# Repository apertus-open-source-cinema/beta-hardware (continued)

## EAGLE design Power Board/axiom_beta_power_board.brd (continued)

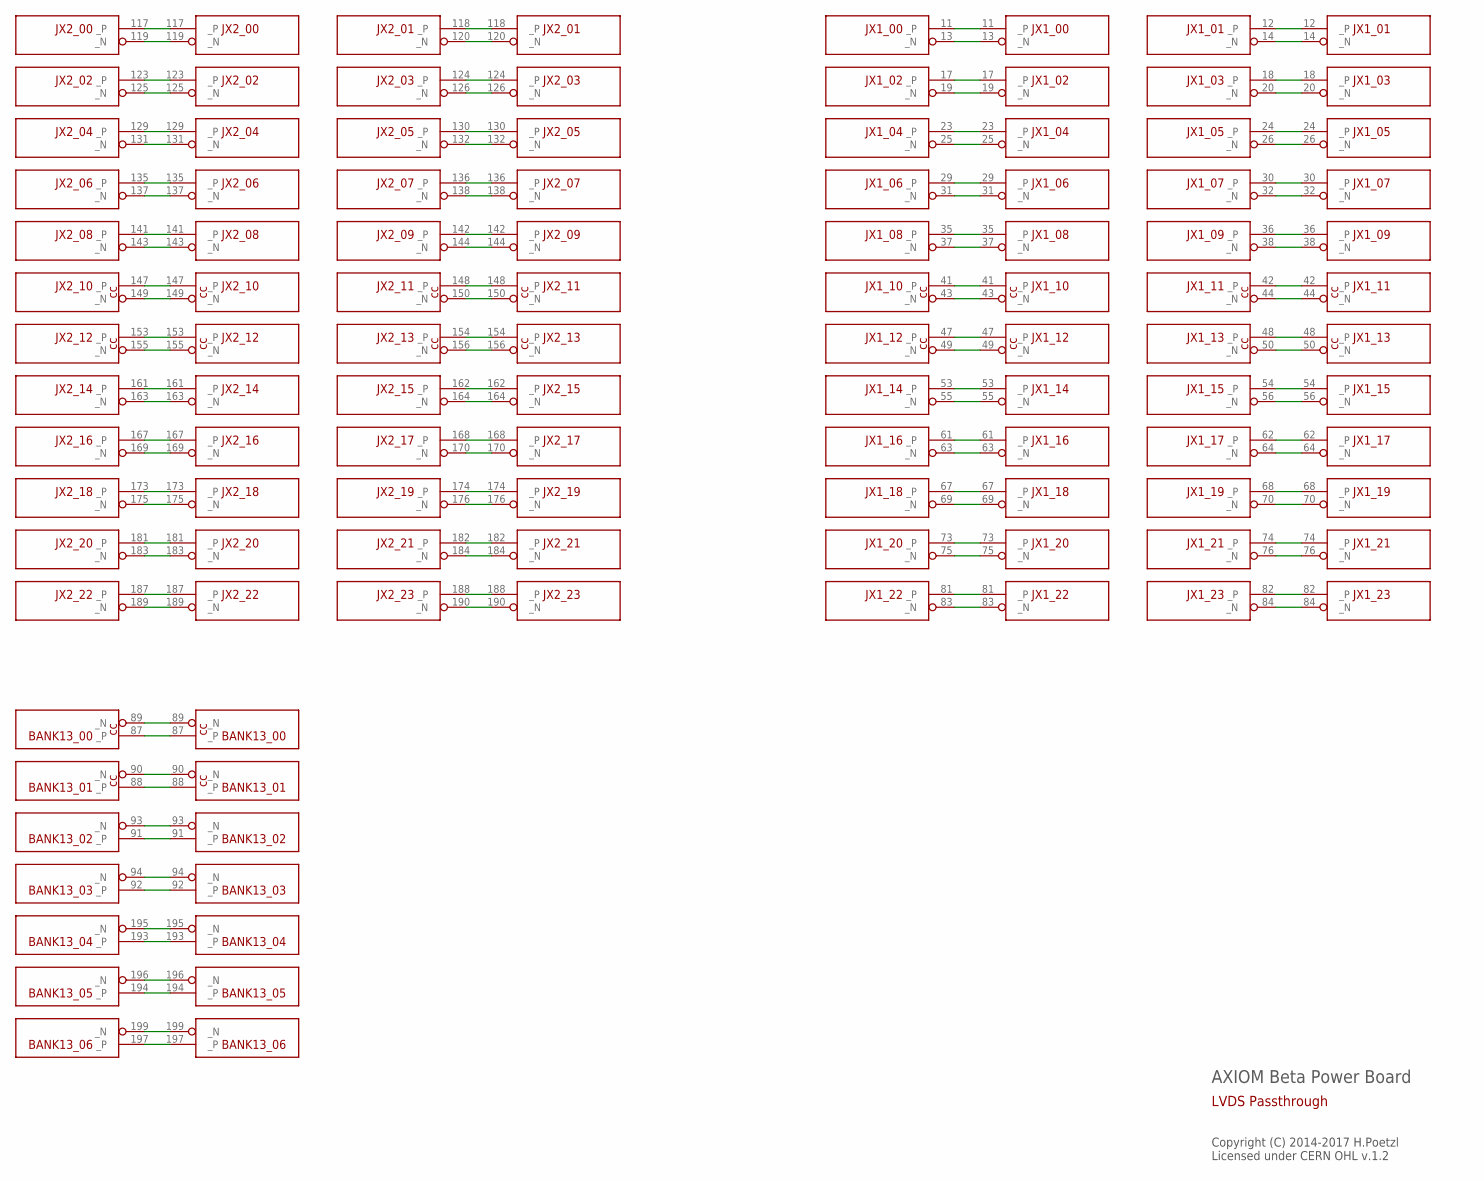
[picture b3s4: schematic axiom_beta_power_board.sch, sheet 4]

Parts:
BETA: µZ-FCI-SOCKET-NOHOLES-R; µZ-SOCKET-NOHOLES-R
ZED: µZ-FCI-CONONLY; µZ-CONONLY

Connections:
BANK13_00_N: BETA.89 (_N), ZED.89 (_N)
BANK13_00_P: BETA.87 (_P), ZED.87 (_P)
BANK13_01_N: BETA.90 (_N), ZED.90 (_N)
BANK13_01_P: BETA.88 (_P), ZED.88 (_P)
BANK13_02_N: BETA.93 (_N), ZED.93 (_N)
BANK13_02_P: BETA.91 (_P), ZED.91 (_P)
BANK13_03_N: BETA.94 (_N), ZED.94 (_N)
BANK13_03_P: BETA.92 (_P), ZED.92 (_P)
BANK13_04_N: BETA.195 (_N), ZED.195 (_N)
BANK13_04_P: BETA.193 (_P), ZED.193 (_P)
BANK13_05_N: BETA.196 (_N), ZED.196 (_N)
BANK13_05_P: BETA.194 (_P), ZED.194 (_P)
BANK13_06_N: BETA.199 (_N), ZED.199 (_N)
BANK13_06_P: BETA.197 (_P), ZED.197 (_P)
JX1_00_N: BETA.13 (_N), ZED.13 (_N)
JX1_00_P: BETA.11 (_P), ZED.11 (_P)
JX1_01_N: BETA.14 (_N), ZED.14 (_N)
JX1_01_P: BETA.12 (_P), ZED.12 (_P)
JX1_02_N: BETA.19 (_N), ZED.19 (_N)
JX1_02_P: BETA.17 (_P), ZED.17 (_P)
JX1_03_N: BETA.20 (_N), ZED.20 (_N)
JX1_03_P: BETA.18 (_P), ZED.18 (_P)
JX1_04_N: BETA.25 (_N), ZED.25 (_N)
JX1_04_P: BETA.23 (_P), ZED.23 (_P)
JX1_05_N: BETA.26 (_N), ZED.26 (_N)
JX1_05_P: BETA.24 (_P), ZED.24 (_P)
JX1_06_N: BETA.31 (_N), ZED.31 (_N)
JX1_06_P: BETA.29 (_P), ZED.29 (_P)
JX1_07_N: BETA.32 (_N), ZED.32 (_N)
JX1_07_P: BETA.30 (_P), ZED.30 (_P)
JX1_08_N: BETA.37 (_N), ZED.37 (_N)
JX1_08_P: BETA.35 (_P), ZED.35 (_P)
JX1_09_N: BETA.38 (_N), ZED.38 (_N)
JX1_09_P: BETA.36 (_P), ZED.36 (_P)
JX1_10_N: BETA.43 (_N), ZED.43 (_N)
JX1_10_P: BETA.41 (_P), ZED.41 (_P)
JX1_11_N: BETA.44 (_N), ZED.44 (_N)
JX1_11_P: BETA.42 (_P), ZED.42 (_P)
JX1_12_N: BETA.49 (_N), ZED.49 (_N)
JX1_12_P: BETA.47 (_P), ZED.47 (_P)
JX1_13_N: BETA.50 (_N), ZED.50 (_N)
JX1_13_P: BETA.48 (_P), ZED.48 (_P)
JX1_14_N: BETA.55 (_N), ZED.55 (_N)
JX1_14_P: BETA.53 (_P), ZED.53 (_P)
JX1_15_N: BETA.56 (_N), ZED.56 (_N)
JX1_15_P: BETA.54 (_P), ZED.54 (_P)
JX1_16_N: BETA.63 (_N), ZED.63 (_N)
JX1_16_P: BETA.61 (_P), ZED.61 (_P)
JX1_17_N: BETA.64 (_N), ZED.64 (_N)
JX1_17_P: BETA.62 (_P), ZED.62 (_P)
JX1_18_N: BETA.69 (_N), ZED.69 (_N)
JX1_18_P: BETA.67 (_P), ZED.67 (_P)
JX1_19_N: BETA.70 (_N), ZED.70 (_N)
JX1_19_P: BETA.68 (_P), ZED.68 (_P)
JX1_20_N: BETA.75 (_N), ZED.75 (_N)
JX1_20_P: BETA.73 (_P), ZED.73 (_P)
JX1_21_N: BETA.76 (_N), ZED.76 (_N)
JX1_21_P: BETA.74 (_P), ZED.74 (_P)
JX1_22_N: BETA.83 (_N), ZED.83 (_N)
JX1_22_P: BETA.81 (_P), ZED.81 (_P)
JX1_23_N: BETA.84 (_N), ZED.84 (_N)
JX1_23_P: BETA.82 (_P), ZED.82 (_P)
JX2_00_N: BETA.119 (_N), ZED.119 (_N)
JX2_00_P: BETA.117 (_P), ZED.117 (_P)
JX2_01_N: BETA.120 (_N), ZED.120 (_N)
JX2_01_P: BETA.118 (_P), ZED.118 (_P)
JX2_02_N: BETA.125 (_N), ZED.125 (_N)
JX2_02_P: BETA.123 (_P), ZED.123 (_P)
JX2_03_N: BETA.126 (_N), ZED.126 (_N)
JX2_03_P: BETA.124 (_P), ZED.124 (_P)
JX2_04_N: BETA.131 (_N), ZED.131 (_N)
JX2_04_P: BETA.129 (_P), ZED.129 (_P)
JX2_05_N: BETA.132 (_N), ZED.132 (_N)
JX2_05_P: BETA.130 (_P), ZED.130 (_P)
JX2_06_N: BETA.137 (_N), ZED.137 (_N)
JX2_06_P: BETA.135 (_P), ZED.135 (_P)
JX2_07_N: BETA.138 (_N), ZED.138 (_N)
JX2_07_P: BETA.136 (_P), ZED.136 (_P)
JX2_08_N: BETA.143 (_N), ZED.143 (_N)
JX2_08_P: BETA.141 (_P), ZED.141 (_P)
JX2_09_N: BETA.144 (_N), ZED.144 (_N)
JX2_09_P: BETA.142 (_P), ZED.142 (_P)
JX2_10_N: BETA.149 (_N), ZED.149 (_N)
JX2_10_P: BETA.147 (_P), ZED.147 (_P)
JX2_11_N: BETA.150 (_N), ZED.150 (_N)
JX2_11_P: BETA.148 (_P), ZED.148 (_P)
JX2_12_N: BETA.155 (_N), ZED.155 (_N)
JX2_12_P: BETA.153 (_P), ZED.153 (_P)
JX2_13_N: BETA.156 (_N), ZED.156 (_N)
JX2_13_P: BETA.154 (_P), ZED.154 (_P)
JX2_14_N: BETA.163 (_N), ZED.163 (_N)
JX2_14_P: BETA.161 (_P), ZED.161 (_P)
JX2_15_N: BETA.164 (_N), ZED.164 (_N)
JX2_15_P: BETA.162 (_P), ZED.162 (_P)
JX2_16_N: BETA.169 (_N), ZED.169 (_N)
JX2_16_P: BETA.167 (_P), ZED.167 (_P)
JX2_17_N: BETA.170 (_N), ZED.170 (_N)
JX2_17_P: BETA.168 (_P), ZED.168 (_P)
JX2_18_N: BETA.175 (_N), ZED.175 (_N)
JX2_18_P: BETA.173 (_P), ZED.173 (_P)
JX2_19_N: BETA.176 (_N), ZED.176 (_N)
JX2_19_P: BETA.174 (_P), ZED.174 (_P)
JX2_20_N: BETA.183 (_N), ZED.183 (_N)
JX2_20_P: BETA.181 (_P), ZED.181 (_P)
JX2_21_N: BETA.184 (_N), ZED.184 (_N)
JX2_21_P: BETA.182 (_P), ZED.182 (_P)
JX2_22_N: BETA.189 (_N), ZED.189 (_N)
JX2_22_P: BETA.187 (_P), ZED.187 (_P)
JX2_23_N: BETA.190 (_N), ZED.190 (_N)
JX2_23_P: BETA.188 (_P), ZED.188 (_P)

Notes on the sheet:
AXIOM Beta Power Board
Copyright (C) 2014-2017 H.Poetzl Licensed under CERN OHL v.1.2
LVDS Passthrough

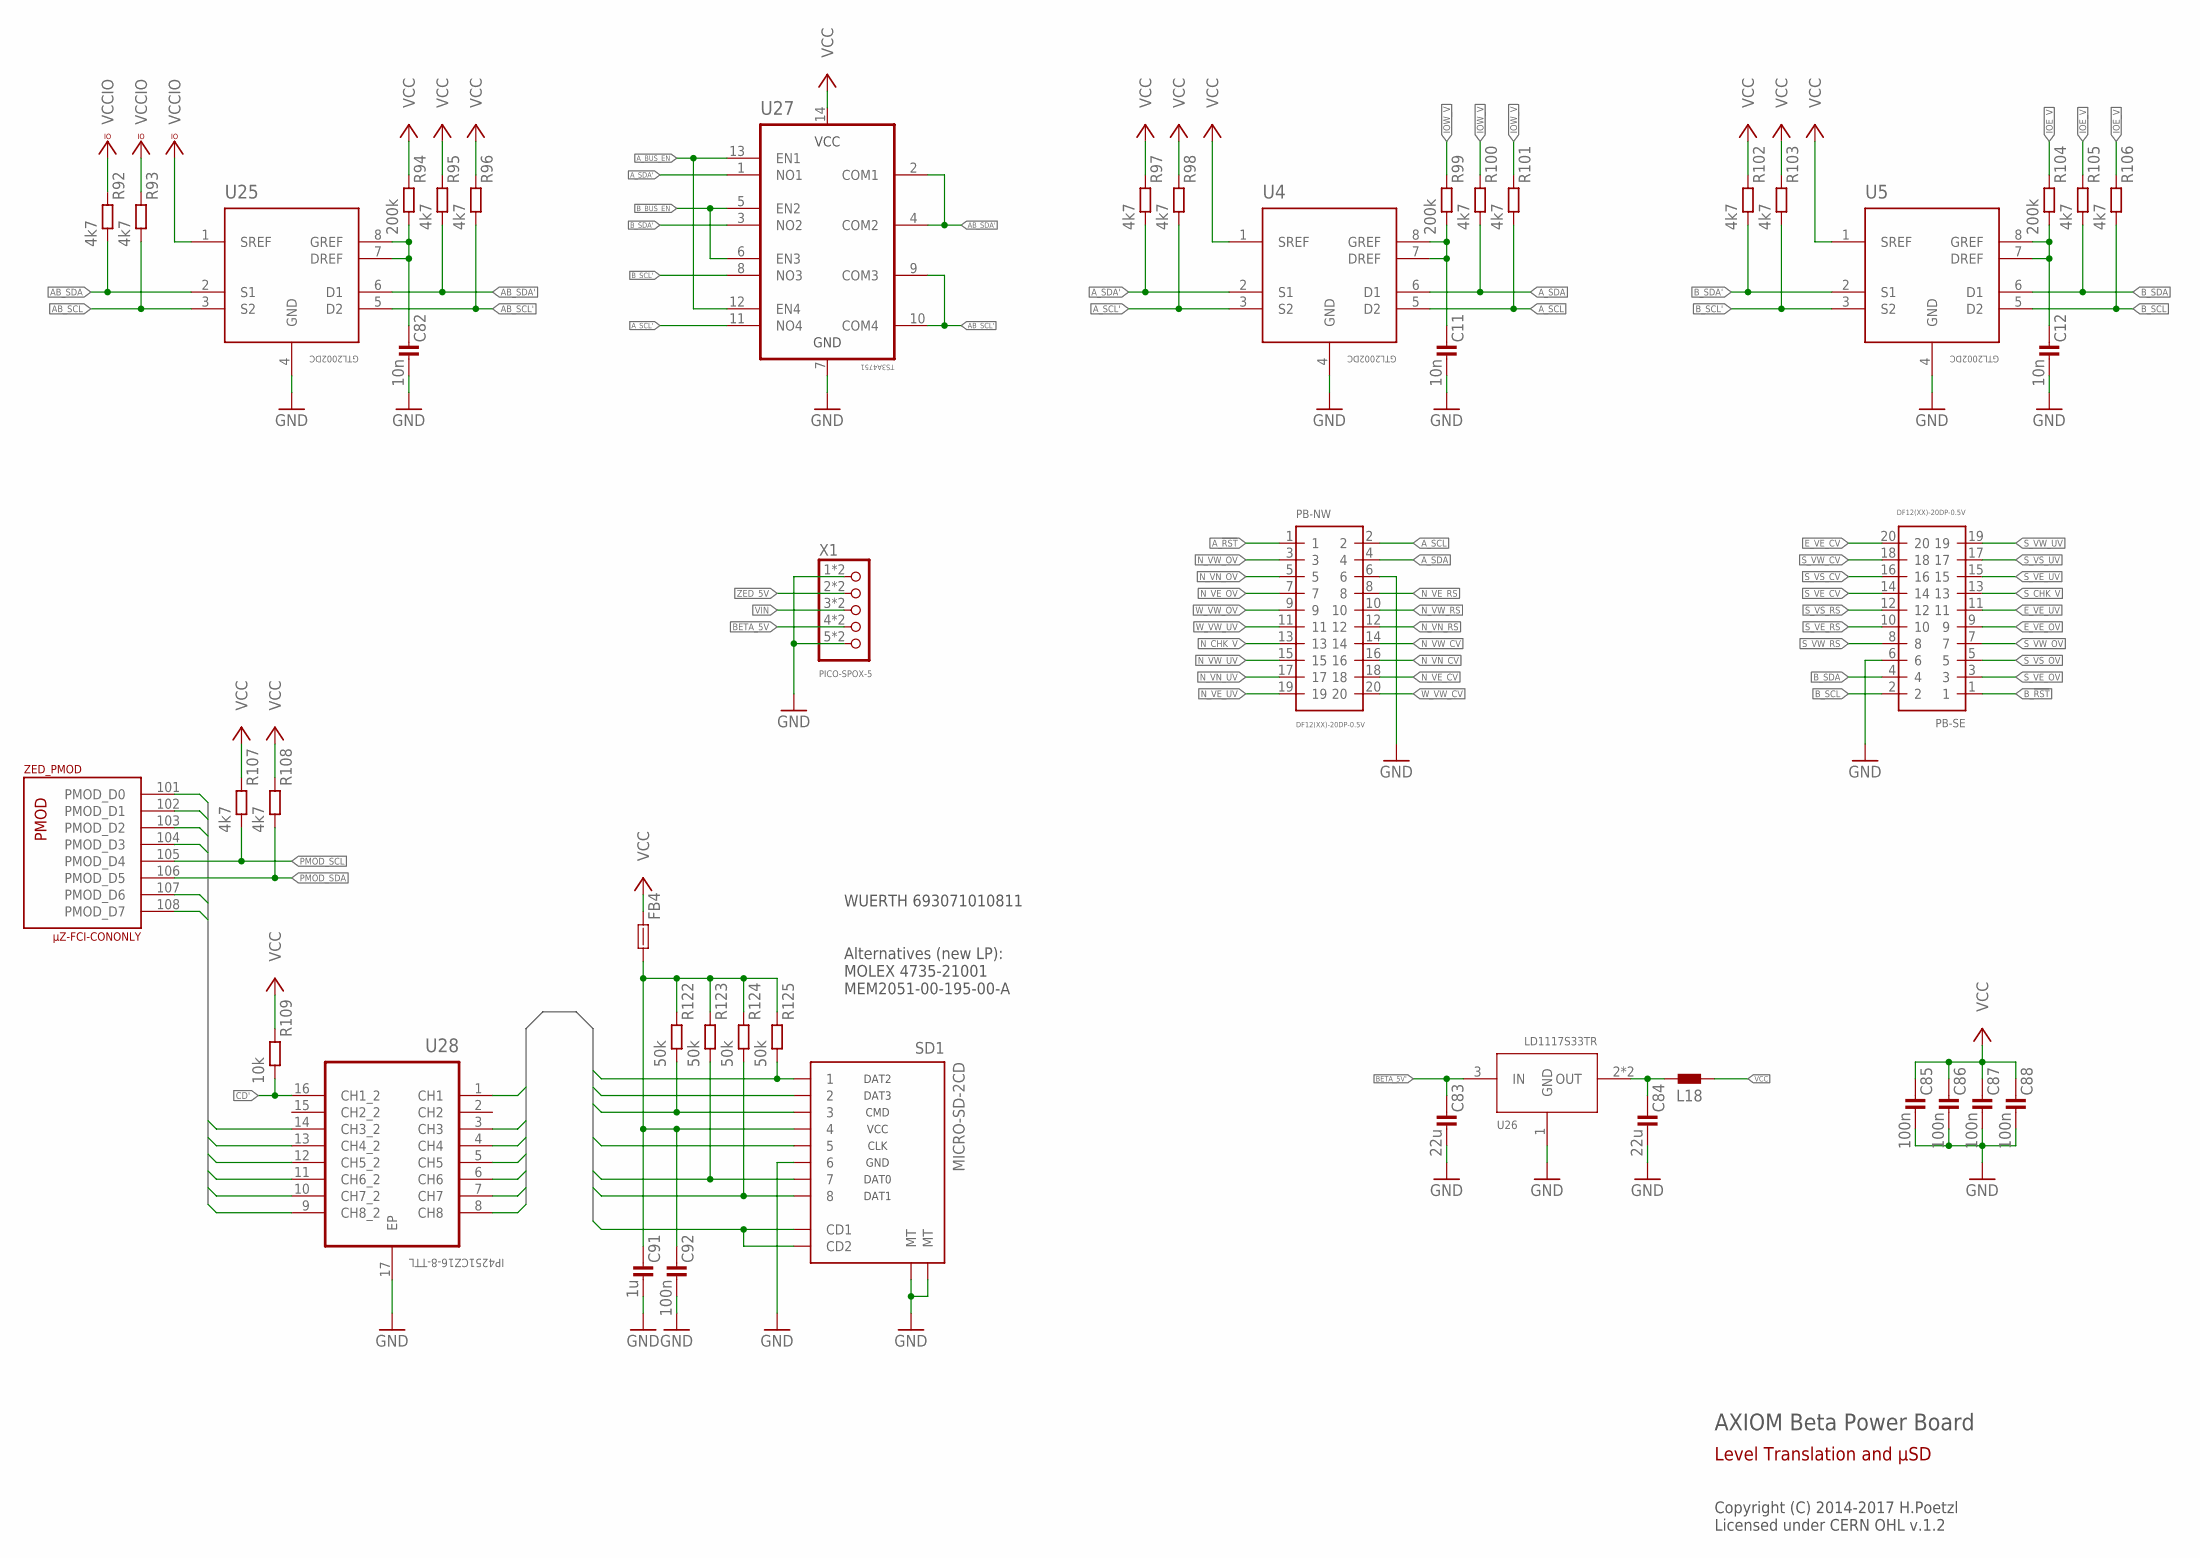
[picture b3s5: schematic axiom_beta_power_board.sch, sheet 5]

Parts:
C11, C12, C82: 10n; 0402-B
C83, C84: 22u; 0805-B
C85, C86, C87, C88, C92: 100n; 0402-B
C91: 1u; 0402-B
FB4: FB0402-B; 0402-B
L18: L0805-A; 0805-A
PB-NW: DF12(XX)-20DP-0.5V
PB-SE: DF12(XX)-20DP-0.5V
R92, R93, R95, R96, R97, R98, R100, R101, R102, R103, R105, R106, R107, R108: 4k7; 0402-B
R94, R99, R104: 200k; 0402-B
R109: 10k; 0402-B
R122, R123, R124, R125: 50k; 0402-B
SD1: MICRO-SD-2CD; TF-MICRO-SD_PP2
U4, U5, U25: GTL2002DC; VSSOP-8
U26: LD1117S33TR; SOT-223
U27: TS3A4751; SOP65P640X120-14N
U28: IP4251CZ16-8-TTL; SON40P135X330X55-17N
X1: PICO-SPOX-5
ZED: µZ-FCI-CONONLY; µZ-CONONLY

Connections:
AB_SCL: R93.2, U25.3 (S2); also elsewhere on the board
AB_SCL': R96.2, U25.5 (D2), U27.9 (COM3), U27.10 (COM4)
AB_SDA: R92.2, U25.2 (S1); also elsewhere on the board
AB_SDA': R95.2, U25.6 (D1), U27.2 (COM1), U27.4 (COM2)
A_!RST: PB-NW.1; also elsewhere on the board
A_BUS_EN: U27.12 (EN4), U27.13 (EN1); also elsewhere on the board
A_SCL: PB-NW.2, R101.2, U4.5 (D2)
A_SCL': R98.2, U4.3 (S2), U27.11 (NO4)
A_SDA: PB-NW.4, R100.2, U4.6 (D1)
A_SDA': R97.2, U4.2 (S1), U27.1 (NO1)
BETA_5V: X1.4, X1.4A (4); also elsewhere on the board
BETA_5V': C83.1, U26.3 (IN); also elsewhere on the board
B_!RST: PB-SE.1; also elsewhere on the board
B_BUS_EN: U27.5 (EN2), U27.6 (EN3); also elsewhere on the board
B_SCL: PB-SE.2, R106.2, U5.5 (D2)
B_SCL': R103.2, U5.3 (S2), U27.8 (NO3)
B_SDA: PB-SE.4, R105.2, U5.6 (D1)
B_SDA': R102.2, U5.2 (S1), U27.3 (NO2)
CD: SD1.CD1, SD1.CD2, U28.1 (CH1)
CD': R109.2, U28.16 (CH1_2); also elsewhere on the board
CLK: SD1.5, U28.6 (CH6)
CMD: R122.2, SD1.3, U28.5 (CH5)
DAT0: R123.2, SD1.7, U28.7 (CH7)
DAT1: R124.2, SD1.8, U28.8 (CH8)
DAT2: R125.2, SD1.1, U28.3 (CH3)
DAT3: SD1.2, U28.4 (CH4)
E_VE_CV: PB-SE.20
E_VE_OV: PB-SE.9
E_VE_UV: PB-SE.11
GND: C11.2, C12.2, C82.2, C83.2, C84.2, C85.2, C86.2, C87.2, C88.2, C91.2, C92.2, PB-NW.6, PB-SE.6, SD1.6, SD1.MT1 (MT), SD1.MT2 (MT), U4.4 (GND), U5.4 (GND), U25.4 (GND), U26.1 (GND), U27.7 (GND), U28.17 (EP), X1.1, X1.1A (1), X1.5, X1.5A (5); also elsewhere on the board
IOE_V: R104.1, R105.1, R106.1; also elsewhere on the board
IOW_V: R99.1, R100.1, R101.1; also elsewhere on the board
unnamed: C91.1, C92.1, FB4.2, R122.1, R123.1, R124.1, R125.1, SD1.4
unnamed: C11.1, R99.2, U4.7 (DREF), U4.8 (GREF)
unnamed: C12.1, R104.2, U5.7 (DREF), U5.8 (GREF)
unnamed: C82.1, R94.2, U25.7 (DREF), U25.8 (GREF)
N_CHK_V: PB-NW.13
N_VE_CV: PB-NW.18
N_VE_OV: PB-NW.7
N_VE_RS: PB-NW.8
N_VE_UV: PB-NW.19
N_VN_CV: PB-NW.16
N_VN_OV: PB-NW.5
N_VN_RS: PB-NW.12
N_VN_UV: PB-NW.17
N_VW_CV: PB-NW.14
N_VW_OV: PB-NW.3
N_VW_RS: PB-NW.10
N_VW_UV: PB-NW.15
PMOD_D0: U28.9 (CH8_2), ZED.101 (PMOD_D0)
PMOD_D1: U28.10 (CH7_2), ZED.102 (PMOD_D1)
PMOD_D2: U28.12 (CH5_2), ZED.103 (PMOD_D2)
PMOD_D3: U28.11 (CH6_2), ZED.104 (PMOD_D3)
PMOD_D6: U28.14 (CH3_2), ZED.107 (PMOD_D6)
PMOD_D7: U28.13 (CH4_2), ZED.108 (PMOD_D7)
PMOD_SCL: R107.2, ZED.105 (PMOD_D4); also elsewhere on the board
PMOD_SDA: R108.2, ZED.106 (PMOD_D5); also elsewhere on the board
REGOUT: C84.1, L18.1, U26.2 (OUT), U26.TER (OUT)
S_CHK_V: PB-SE.13
S_VE_CV: PB-SE.14
S_VE_OV: PB-SE.3
S_VE_RS: PB-SE.10
S_VE_UV: PB-SE.15
S_VS_CV: PB-SE.16
S_VS_OV: PB-SE.5
S_VS_RS: PB-SE.12
S_VS_UV: PB-SE.17
S_VW_CV: PB-SE.18
S_VW_OV: PB-SE.7
S_VW_RS: PB-SE.8
S_VW_UV: PB-SE.19
VCC: C85.1, C86.1, C87.1, C88.1, FB4.1, L18.2, R94.1, R95.1, R96.1, R97.1, R98.1, R102.1, R103.1, R107.1, R108.1, R109.1, U4.1 (SREF), U5.1 (SREF), U27.14 (VCC); also elsewhere on the board
VCCIO: R92.1, R93.1, U25.1 (SREF); also elsewhere on the board
VIN: X1.3, X1.3A (3)
W_VW_CV: PB-NW.20
W_VW_OV: PB-NW.9
W_VW_UV: PB-NW.11
ZED_5V: X1.2, X1.2A (2); also elsewhere on the board

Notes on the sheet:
AXIOM Beta Power Board
Copyright (C) 2014-2017 H.Poetzl Licensed under CERN OHL v.1.2
Level Translation and µSD
WUERTH 693071010811 Alternatives (new LP): MOLEX 4735-21001 MEM2051-00-195-00-A

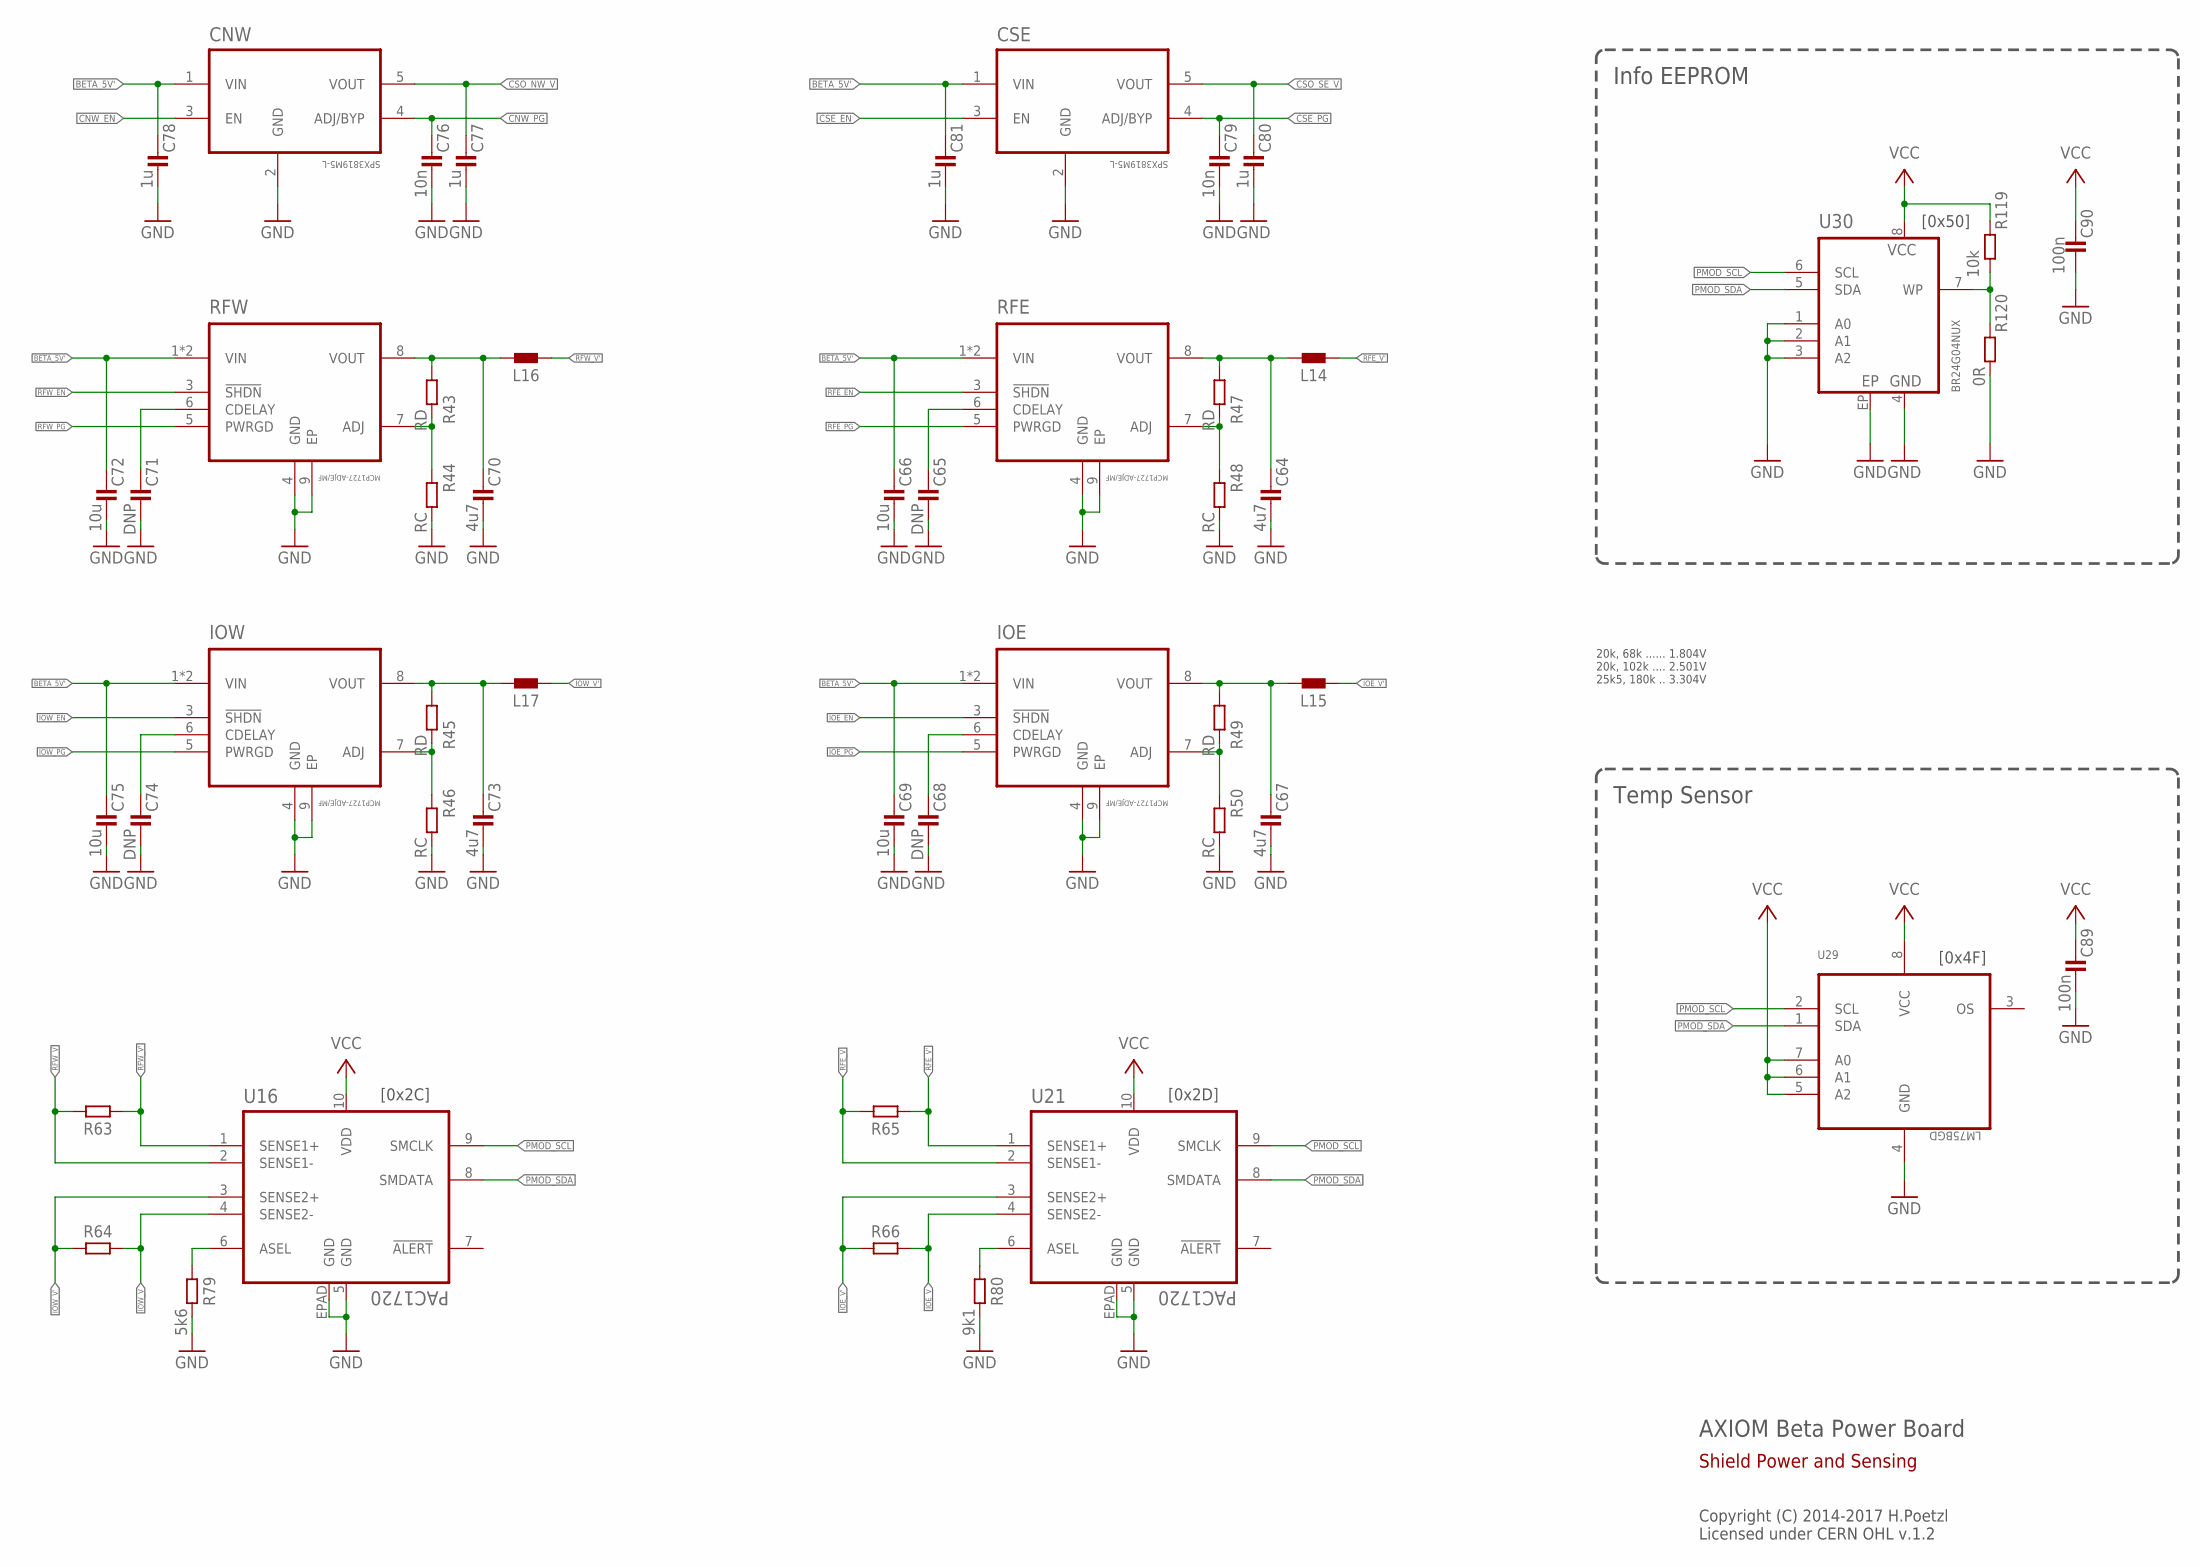
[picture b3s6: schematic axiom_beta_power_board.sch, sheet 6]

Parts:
C64, C67, C70, C73: 4u7; 0603-B
C65, C68, C71, C74: DNP; 0402-B
C66, C69, C72, C75: 10u; 0603-B
C76, C79: 10n; 0402-B
C77, C78, C80, C81: 1u; 0402-B
C89, C90: 100n; 0402-B
CNW: SPX3819M5-L; SOT95P280X145-5N
CSE: SPX3819M5-L; SOT95P280X145-5N
IOE: MCP1727-ADJE/MF; DFN65P300X300X100-9N
IOW: MCP1727-ADJE/MF; DFN65P300X300X100-9N
L14, L15, L16, L17: L0805-B; 0805-B
R43, R45, R47, R49: RD; 0402-B
R44, R46, R48, R50: RC; 0402-B
R63, R64, R65, R66: R1206-B; 1206-B
R79: 5k6; 0402-B
R80: 9k1; 0402-B
R119: 10k; 0402-B
R120: 0R; 0402-B
RFE: MCP1727-ADJE/MF; DFN65P300X300X100-9N
RFW: MCP1727-ADJE/MF; DFN65P300X300X100-9N
U16, U21: PAC1720; DFN3X3_10LEAD
U29: LM75BGD; SOT996-2/3
U30: BR24G04NUX; DFN200X300X100-9N

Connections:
BETA_5V': C66.1, C69.1, C72.1, C75.1, C78.1, C81.1, CNW.1 (VIN), CSE.1 (VIN), IOE.1 (VIN), IOE.2 (VIN), IOW.1 (VIN), IOW.2 (VIN), RFE.1 (VIN), RFE.2 (VIN), RFW.1 (VIN), RFW.2 (VIN); also elsewhere on the board
CNW_EN: CNW.3 (EN); also elsewhere on the board
CNW_PG: C76.1, CNW.4 (ADJ/BYP); also elsewhere on the board
CSE_EN: CSE.3 (EN); also elsewhere on the board
CSE_PG: C79.1, CSE.4 (ADJ/BYP); also elsewhere on the board
CSO_NW_V: C77.1, CNW.5 (VOUT); also elsewhere on the board
CSO_SE_V: C80.1, CSE.5 (VOUT); also elsewhere on the board
GND: C64.2, C65.2, C66.2, C67.2, C68.2, C69.2, C70.2, C71.2, C72.2, C73.2, C74.2, C75.2, C76.2, C77.2, C78.2, C79.2, C80.2, C81.2, C89.2, C90.2, CNW.2 (GND), CSE.2 (GND), IOE.4 (GND), IOE.9 (EP), IOW.4 (GND), IOW.9 (EP), R44.2, R46.2, R48.2, R50.2, R79.2, R80.2, R120.2, RFE.4 (GND), RFE.9 (EP), RFW.4 (GND), RFW.9 (EP), U16.5 (GND), U16.EPAD (GND), U21.5 (GND), U21.EPAD (GND), U29.4 (GND), U30.1 (A0), U30.2 (A1), U30.3 (A2), U30.4 (GND), U30.EP; also elsewhere on the board
IOE_EN: IOE.3 (!SHDN); also elsewhere on the board
IOE_PG: IOE.5 (PWRGD); also elsewhere on the board
IOE_V: R66.2, U21.4 (SENSE2-); also elsewhere on the board
IOE_V': L15.2, R66.1, U21.3 (SENSE2+)
IOW_EN: IOW.3 (!SHDN); also elsewhere on the board
IOW_PG: IOW.5 (PWRGD); also elsewhere on the board
IOW_V: R64.2, U16.4 (SENSE2-); also elsewhere on the board
IOW_V': L17.2, R64.1, U16.3 (SENSE2+)
unnamed: R119.2, R120.1, U30.7 (WP)
unnamed: C64.1, L14.1, R47.1, RFE.8 (VOUT)
unnamed: R47.2, R48.1, RFE.7 (ADJ)
unnamed: C65.1, RFE.6 (CDELAY)
unnamed: C67.1, IOE.8 (VOUT), L15.1, R49.1
unnamed: IOE.7 (ADJ), R49.2, R50.1
unnamed: C68.1, IOE.6 (CDELAY)
unnamed: C70.1, L16.1, R43.1, RFW.8 (VOUT)
unnamed: R43.2, R44.1, RFW.7 (ADJ)
unnamed: C71.1, RFW.6 (CDELAY)
unnamed: C73.1, IOW.8 (VOUT), L17.1, R45.1
unnamed: IOW.7 (ADJ), R45.2, R46.1
unnamed: C74.1, IOW.6 (CDELAY)
unnamed: R79.1, U16.6 (ASEL)
unnamed: R80.1, U21.6 (ASEL)
PMOD_SCL: U16.9 (SMCLK), U21.9 (SMCLK), U29.2 (SCL), U30.6 (SCL); also elsewhere on the board
PMOD_SDA: U16.8 (SMDATA), U21.8 (SMDATA), U29.1 (SDA), U30.5 (SDA); also elsewhere on the board
RFE_EN: RFE.3 (!SHDN); also elsewhere on the board
RFE_PG: RFE.5 (PWRGD); also elsewhere on the board
RFE_V: R65.2, U21.2 (SENSE1-); also elsewhere on the board
RFE_V': L14.2, R65.1, U21.1 (SENSE1+)
RFW_EN: RFW.3 (!SHDN); also elsewhere on the board
RFW_PG: RFW.5 (PWRGD); also elsewhere on the board
RFW_V: R63.2, U16.2 (SENSE1-); also elsewhere on the board
RFW_V': L16.2, R63.1, U16.1 (SENSE1+)
VCC: C89.1, C90.1, R119.1, U16.10 (VDD), U21.10 (VDD), U29.5 (A2), U29.6 (A1), U29.7 (A0), U29.8 (VCC), U30.8 (VCC); also elsewhere on the board

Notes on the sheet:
AXIOM Beta Power Board
Copyright (C) 2014-2017 H.Poetzl Licensed under CERN OHL v.1.2
Shield Power and Sensing
20k, 68k ...... 1.804V 20k, 102k .... 2.501V 25k5, 180k .. 3.304V
[0x2C]
[0x2D]
[0x4F]
Info EEPROM
[0x50]
Temp Sensor

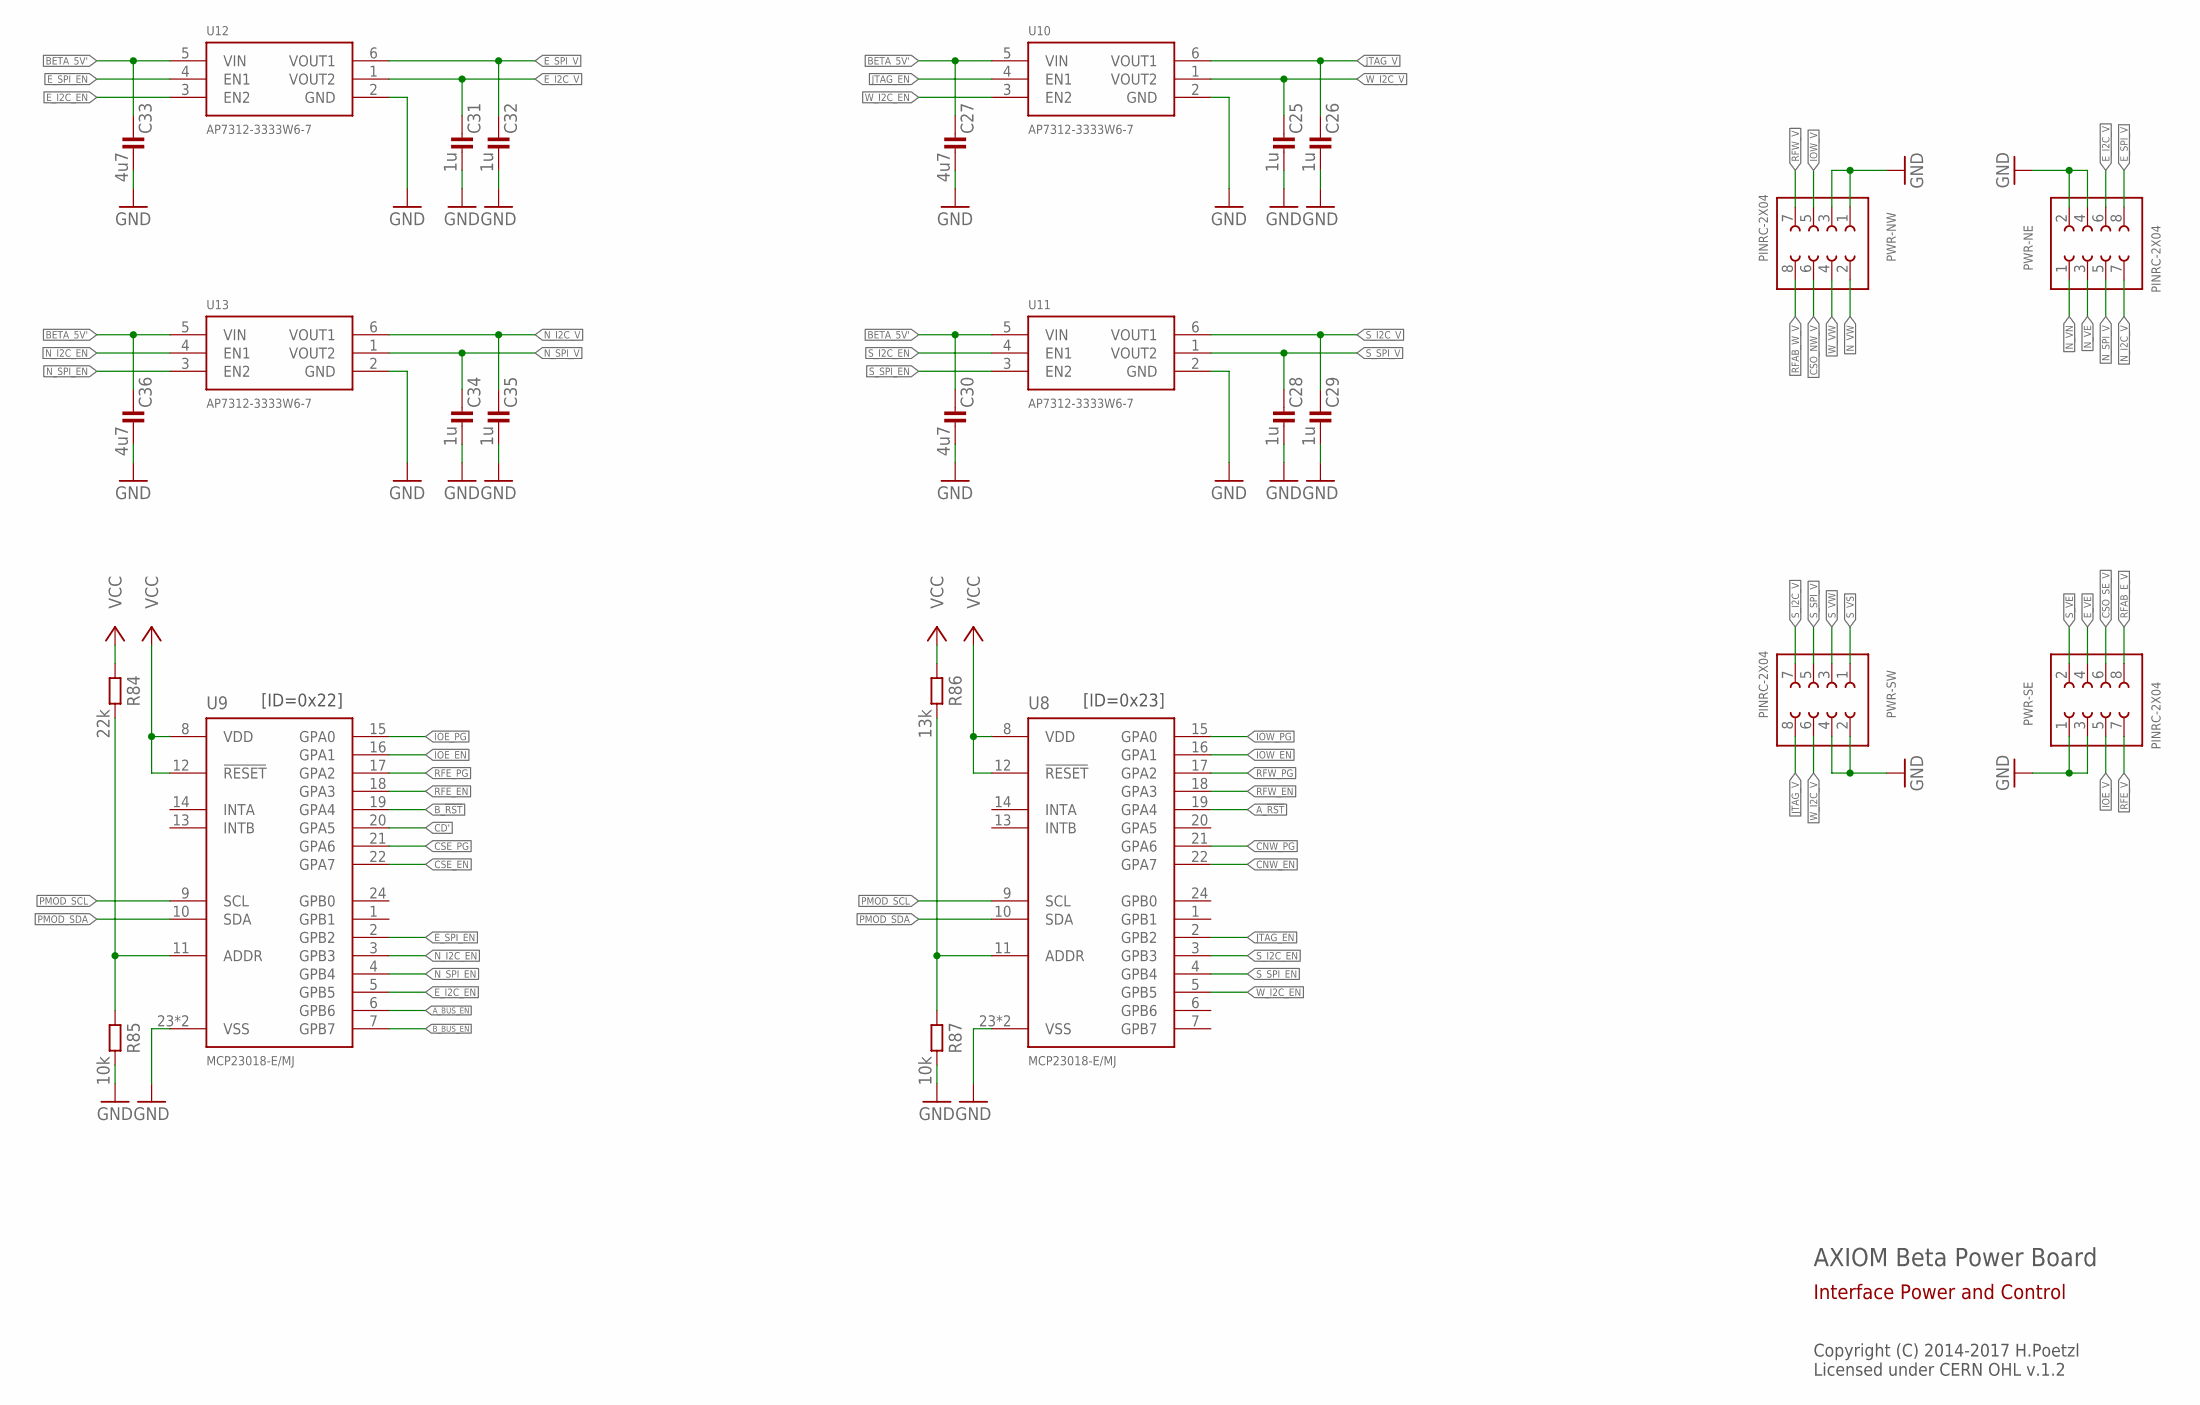
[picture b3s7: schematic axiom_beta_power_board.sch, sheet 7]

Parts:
C25, C26, C28, C29, C31, C32, C34, C35: 1u; 0402-B
C27, C30, C33, C36: 4u7; 0603-B
PWR-NE: PINRC-2X04; R2X04
PWR-NW: PINRC-2X04; R2X04
PWR-SE: PINRC-2X04; R2X04
PWR-SW: PINRC-2X04; R2X04
R84: 22k; 0402-B
R85, R87: 10k; 0402-B
R86: 13k; 0402-B
U8, U9: MCP23018-E/MJ; QFN50P400X400X80-25N
U10, U11, U12, U13: AP7312-3333W6-7; SOT23-6

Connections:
A_!RST: U8.19 (GPA4); also elsewhere on the board
A_BUS_EN: U9.6 (GPB6); also elsewhere on the board
BETA_5V': C27.1, C30.1, C33.1, C36.1, U10.5 (VIN), U11.5 (VIN), U12.5 (VIN), U13.5 (VIN); also elsewhere on the board
B_!RST: U9.19 (GPA4); also elsewhere on the board
B_BUS_EN: U9.7 (GPB7); also elsewhere on the board
CD': U9.20 (GPA5); also elsewhere on the board
CNW_EN: U8.22 (GPA7); also elsewhere on the board
CNW_PG: U8.21 (GPA6); also elsewhere on the board
CSE_EN: U9.22 (GPA7); also elsewhere on the board
CSE_PG: U9.21 (GPA6); also elsewhere on the board
CSO_NW_V: PWR-NW.6; also elsewhere on the board
CSO_SE_V: PWR-SE.6; also elsewhere on the board
E_I2C_EN: U9.5 (GPB5), U12.3 (EN2)
E_I2C_V: C31.1, PWR-NE.6, U12.1 (VOUT2)
E_SPI_EN: U9.2 (GPB2), U12.4 (EN1)
E_SPI_V: C32.1, PWR-NE.8, U12.6 (VOUT1)
E_VE: PWR-SE.4; also elsewhere on the board
GND: C25.2, C26.2, C27.2, C28.2, C29.2, C30.2, C31.2, C32.2, C33.2, C34.2, C35.2, C36.2, PWR-NE.2, PWR-NE.4, PWR-NW.1, PWR-NW.3, PWR-SE.1, PWR-SE.3, PWR-SW.2, PWR-SW.4, R85.2, R87.2, U8.23 (VSS), U8.25 (VSS), U9.23 (VSS), U9.25 (VSS), U10.2 (GND), U11.2 (GND), U12.2 (GND), U13.2 (GND); also elsewhere on the board
IOE_EN: U9.16 (GPA1); also elsewhere on the board
IOE_PG: U9.15 (GPA0); also elsewhere on the board
IOE_V: PWR-SE.5; also elsewhere on the board
IOW_EN: U8.16 (GPA1); also elsewhere on the board
IOW_PG: U8.15 (GPA0); also elsewhere on the board
IOW_V: PWR-NW.5; also elsewhere on the board
JTAG_EN: U8.2 (GPB2), U10.4 (EN1)
JTAG_V: C26.1, PWR-SW.8, U10.6 (VOUT1)
unnamed: R84.2, R85.1, U9.11 (ADDR)
unnamed: R86.2, R87.1, U8.11 (ADDR)
N_I2C_EN: U9.3 (GPB3), U13.4 (EN1)
N_I2C_V: C35.1, PWR-NE.7, U13.6 (VOUT1)
N_SPI_EN: U9.4 (GPB4), U13.3 (EN2)
N_SPI_V: C34.1, PWR-NE.5, U13.1 (VOUT2)
N_VE: PWR-NE.3; also elsewhere on the board
N_VN: PWR-NE.1; also elsewhere on the board
N_VW: PWR-NW.2; also elsewhere on the board
PMOD_SCL: U8.9 (SCL), U9.9 (SCL); also elsewhere on the board
PMOD_SDA: U8.10 (SDA), U9.10 (SDA); also elsewhere on the board
RFAB_E_V: PWR-SE.8
RFAB_W_V: PWR-NW.8
RFE_EN: U9.18 (GPA3); also elsewhere on the board
RFE_PG: U9.17 (GPA2); also elsewhere on the board
RFE_V: PWR-SE.7; also elsewhere on the board
RFW_EN: U8.18 (GPA3); also elsewhere on the board
RFW_PG: U8.17 (GPA2); also elsewhere on the board
RFW_V: PWR-NW.7; also elsewhere on the board
S_I2C_EN: U8.3 (GPB3), U11.4 (EN1)
S_I2C_V: C29.1, PWR-SW.7, U11.6 (VOUT1)
S_SPI_EN: U8.4 (GPB4), U11.3 (EN2)
S_SPI_V: C28.1, PWR-SW.5, U11.1 (VOUT2)
S_VE: PWR-SE.2; also elsewhere on the board
S_VS: PWR-SW.1; also elsewhere on the board
S_VW: PWR-SW.3; also elsewhere on the board
VCC: R84.1, R86.1, U8.8 (VDD), U8.12 (!RESET), U9.8 (VDD), U9.12 (!RESET); also elsewhere on the board
W_I2C_EN: U8.5 (GPB5), U10.3 (EN2)
W_I2C_V: C25.1, PWR-SW.6, U10.1 (VOUT2)
W_VW: PWR-NW.4; also elsewhere on the board

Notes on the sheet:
AXIOM Beta Power Board
Copyright (C) 2014-2017 H.Poetzl Licensed under CERN OHL v.1.2
Interface Power and Control
[ID=0x22]
[ID=0x23]
